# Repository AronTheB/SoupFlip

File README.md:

# SoupFlip 
## SoupFlip is a basic PCB coin that has 2 leds (heads or tails) or in this version left paw and right paw. You can activate 1 randomly by pressing the button. It is powered by a 2023 coin cell
made for Fallout

## PCB

## 3D
Front

<br></br>
Back

Username: Aron

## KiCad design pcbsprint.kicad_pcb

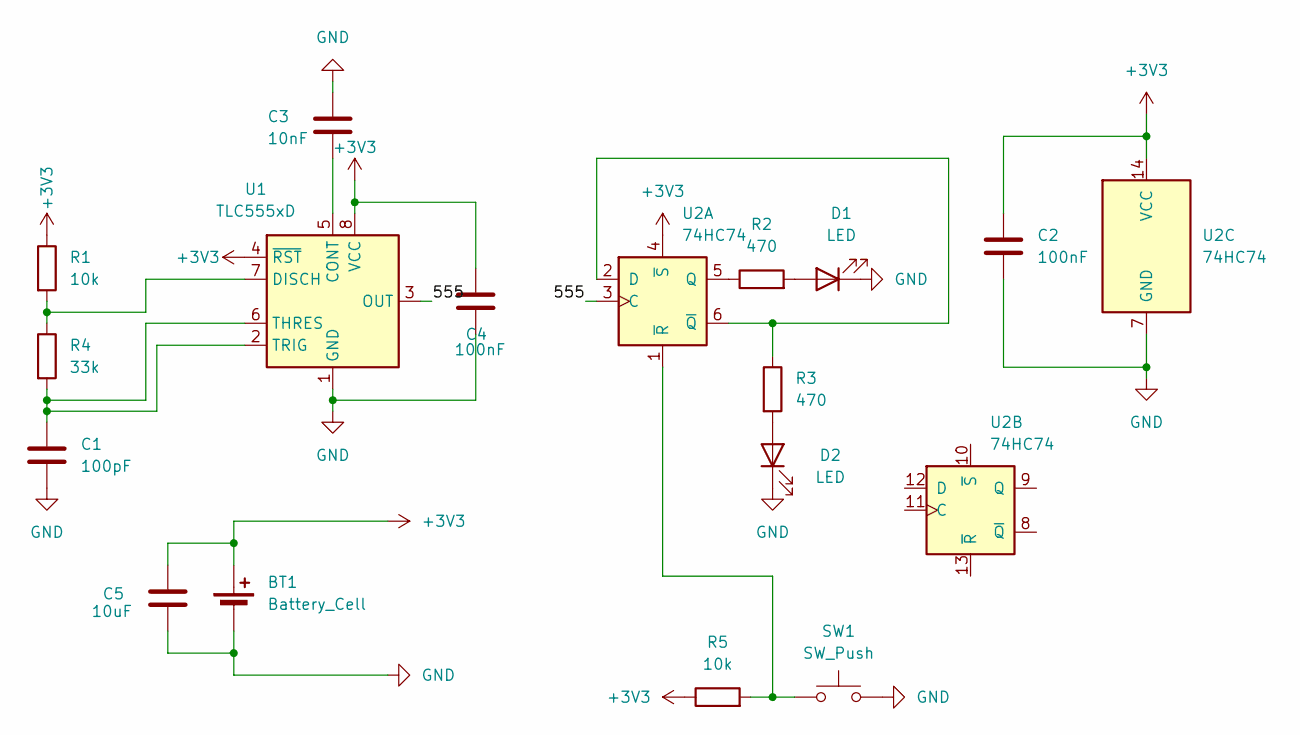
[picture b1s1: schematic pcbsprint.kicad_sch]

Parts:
BT1: Battery_Cell; BatteryHolder_Keystone_3002_1x2032
C1: 100pF; C_0603_1608Metric
C2, C4: 100nF; C_0603_1608Metric
C3: 10nF; C_0603_1608Metric
C5: 10uF; C_0805_2012Metric
D1, D2: LED; LED_1206_3216Metric
R1, R5: 10k; R_0603_1608Metric
R2, R3: 470; R_0603_1608Metric
R4: 33k; R_0603_1608Metric
SW1: SW_Push; SW_SPST_TL3342
U1: TLC555xD; SOIC-8_3.9x4.9mm_P1.27mm
U2: 74HC74; SOIC-14_3.9x8.7mm_P1.27mm

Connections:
+3V3: BT1.1 (+), C2.1, C4.1, C5.1, R1.1, R5.1, U1.4 (~RST), U1.8 (VCC), U2.4 (~S), U2.14 (VCC)
/555: U1.3 (OUT), U2.3 (C)
GND: BT1.2 (-), C1.2, C2.2, C3.1, C4.2, C5.2, D1.1 (K), D2.1 (K), SW1.2, U1.1 (GND), U2.7 (GND)
unnamed: D1.2 (A), R2.2
unnamed: D2.2 (A), R3.2
unnamed: C3.2, U1.5 (CONT)
unnamed: R1.2, R4.1, U1.7 (DISCH)
unnamed: C1.1, R4.2, U1.2 (TRIG), U1.6 (THRES)
unnamed: R3.1, U2.2 (D), U2.6 (~Q)
unnamed: R2.1, U2.5 (Q)
unnamed: R5.2, SW1.1, U2.1 (~R)

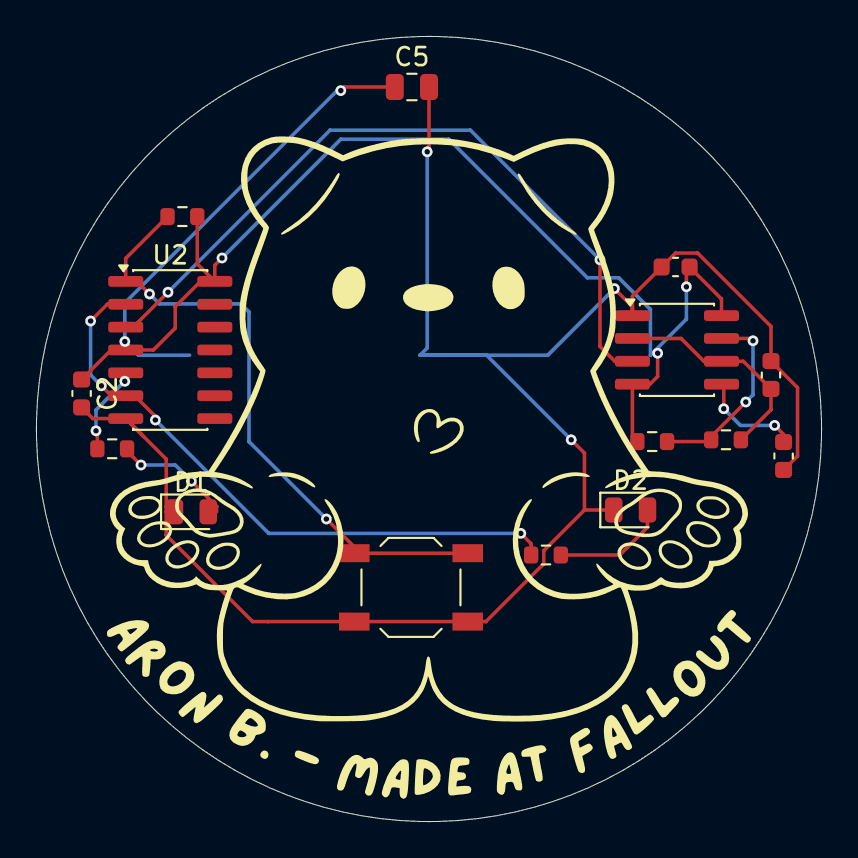
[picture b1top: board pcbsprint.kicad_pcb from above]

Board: 2 copper layers, 43.6 x 43.6 mm, 16 parts (1 on the bottom side), 11 nets.

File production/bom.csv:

Designator,Footprint,Quantity,Value,LCSC Part #
BT1,BatteryHolder_Keystone_3002_1x2032,1,Battery_Cell,
C1,0603,1,100pF,
"C2, C4",0603,2,100nF,
C3,0603,1,10nF,
C5,0805,1,10uF,
"D1,",0805,2,LED,
"D2,",0805,2,LED,
"R1, R5",0603,2,10k,
"R2, R3",0603,2,470,
R4,0603,1,33k,
SW1,SW_SPST_TL3342,1,SW_Push,
U1,SOIC-8_3.9x4.9mm_P1.27mm,1,TLC555xD,
U2,SOIC-14_3.9x8.7mm_P1.27mm,1,74HC74,
